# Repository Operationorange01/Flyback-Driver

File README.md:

# Flyback Driver

This is a driver for a High Voltage Flyback Transformer.

We are planning on using it in the next stage in our research on EHD propulsion. You can read our preprint from last year here: https://doi.org/10.31224/6625

## Features:

- Variable duty cycle
- Variable frequency
- Current/Voltage Sensing
- Current/Voltage Regulating 6V to 25V, digitally adjustable via 12-bit DAC about 5mV resolution
- Rotary encoder for control
- OLED Display
- Indicator Lights
- Soft Startup
- Hardware overcurrent protection, independent of firmware
- Latching fault shutdown
- Adjustable trip threshold
- RCD clamp with tunable clamp voltage

## PCB

Made in KiCad. The full schematic is in [assets/schematic.pdf](assets/schematic.pdf).

Main parts:

- **MCU:** STM32F103C8T6
- **Flyback switch:** IRFP460 (500V, 20A) driven by a UCC27511A gate driver
- **Supply regulation:** LM5117 buck controller with two MCP4725 12-bit DACs for digital voltage/current setpoints
- **Sensing:** INA226 current/voltage monitor
- **Protection:** LM393 comparator + 74HC132 latch for hardware overcurrent shutdown
- **Logic rails:** LM2596 and TPS62130 bucks

Custom footprints are in [pcb/libraries](pcb/libraries).

## Firmware

made some basic firmware but is still untested

**disclaimer, most of the firmware was made using the help of ai because I don't know enough c**

## BOM

The full BOM with reference designators, Digi-Key part numbers and datasheets is in [BOM.csv](BOM.csv). Parts on Digi-Key come to about **$94**.

Not on the Digi-Key order yet:

- 1x 0.91" 128x32 I2C OLED (U4)
- 1x 2x4 2.54mm pin header (J1)
- 1x 1x5 2.54mm pin header (J2)
- 16x test points (TP1–TP16)

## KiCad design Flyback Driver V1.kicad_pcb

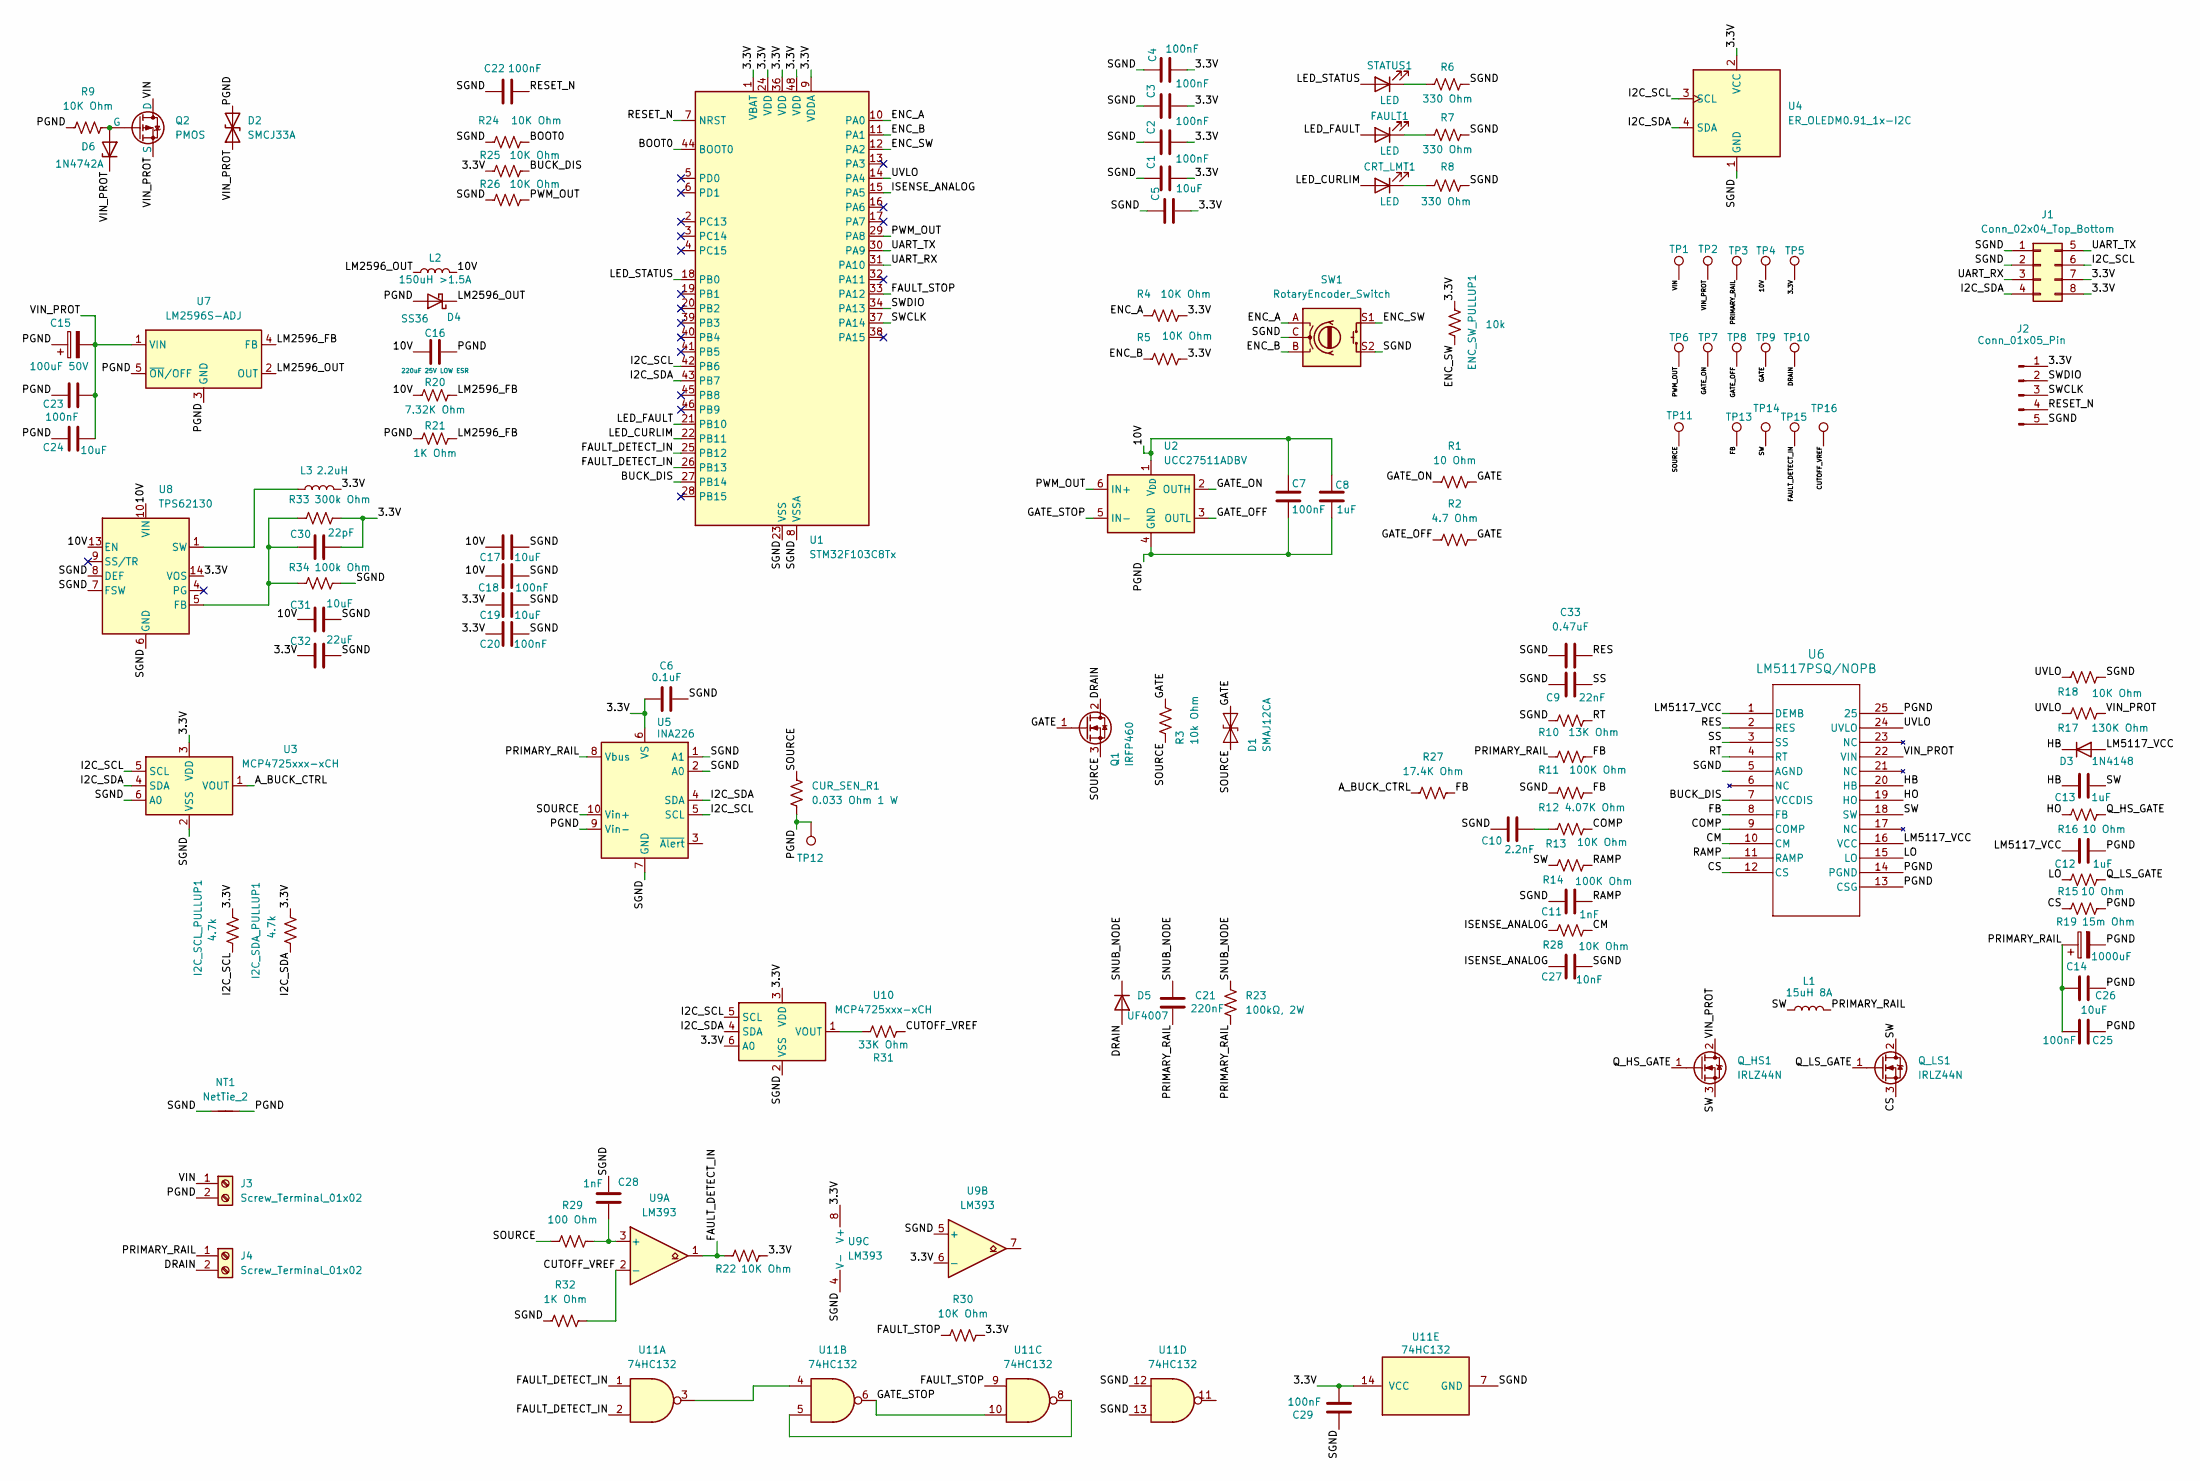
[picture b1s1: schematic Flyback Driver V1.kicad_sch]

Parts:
C1, C2, C3, C4, C7, C18, C20, C22, C23, C25, C29: 100nF; C_0805_2012Metric_Pad1.18x1.45mm_HandSolder
C5, C17, C19, C31: 10uF; C_0805_2012Metric_Pad1.18x1.45mm_HandSolder
C6: 0.1uF; C_0805_2012Metric_Pad1.18x1.45mm_HandSolder
C8, C12, C13: 1uF; C_0805_2012Metric_Pad1.18x1.45mm_HandSolder
C9: 22nF; C_0805_2012Metric_Pad1.18x1.45mm_HandSolder
C10: 2.2nF; C_0805_2012Metric_Pad1.18x1.45mm_HandSolder
C11, C28: 1nF; C_0805_2012Metric_Pad1.18x1.45mm_HandSolder
C14: 1000uF; CP_Radial_D12.5mm_P5.00mm
C15: 100uF 50V; CP_Radial_D8.0mm_P3.50mm
C16: 220uF 25V LOW ESR; CP_Radial_D8.0mm_P3.50mm
C21: 220nF; C_Rect_L18.0mm_W5.0mm_P15.00mm_FKS3_FKP3
C24, C26: 10uF; C_1210_3225Metric_Pad1.33x2.70mm_HandSolder
C27: 10nF; C_0805_2012Metric_Pad1.18x1.45mm_HandSolder
C30: 22pF; C_0805_2012Metric_Pad1.18x1.45mm_HandSolder
C32: 22uF; C_0805_2012Metric_Pad1.18x1.45mm_HandSolder
C33: 0.47uF; C_0805_2012Metric_Pad1.18x1.45mm_HandSolder
CRT_LMT1: LED; LED_0805_2012Metric_Pad1.15x1.40mm_HandSolder
CUR_SEN_R1: 0.033 Ohm 1 W; R_2512_6332Metric_Pad1.40x3.35mm_HandSolder
D1: SMAJ12CA; D_SMA
D2: SMCJ33A; D_SMC
D3: 1N4148; D_DO-35_SOD27_P7.62mm_Horizontal
D4: SS36; D_SMC
D5: UF4007; D_DO-41_SOD81_P10.16mm_Horizontal
D6: 1N4742A; D_DO-41_SOD81_P10.16mm_Horizontal
ENC_SW_PULLUP1: 10k; R_0805_2012Metric_Pad1.20x1.40mm_HandSolder
FAULT1: LED; LED_0805_2012Metric_Pad1.15x1.40mm_HandSolder
I2C_SCL_PULLUP1, I2C_SDA_PULLUP1: 4.7k; R_0805_2012Metric_Pad1.20x1.40mm_HandSolder
J1: Conn_02x04_Top_Bottom; PinHeader_2x04_P2.54mm_Vertical
J2: Conn_01x05_Pin; PinHeader_1x05_P2.54mm_Vertical
J3, J4: Screw_Terminal_01x02; TerminalBlock_Phoenix_MKDS-3-2-5.08_1x02_P5.08mm_Horizontal
L1: 15uH 8A; L_Wurth_WE-XHMA-1090
L2: 150uH >1.5A; INDM125125X800N
L3: 2.2uH; L_Taiyo-Yuden_LCXND4040
NT1: NetTie_2; NetTie-2_SMD_Pad0.5mm
Q1: IRFP460; TO-247-3_Vertical
Q2: PMOS; TO-220-3_Vertical
Q_HS1: IRLZ44N; TO-220-3_Vertical
Q_LS1: IRLZ44N; TO-220-3_Vertical
R1, R15, R16: 10 Ohm; R_0805_2012Metric_Pad1.20x1.40mm_HandSolder
R2: 4.7 Ohm; R_0805_2012Metric_Pad1.20x1.40mm_HandSolder
R3: 10k Ohm; R_0805_2012Metric_Pad1.20x1.40mm_HandSolder
R4, R5, R9, R13, R18, R22, R24, R25, R26, R28, R30: 10K Ohm; R_0805_2012Metric_Pad1.20x1.40mm_HandSolder
R6, R7, R8: 330 Ohm; R_0805_2012Metric_Pad1.20x1.40mm_HandSolder
R10: 13K Ohm; R_0805_2012Metric_Pad1.20x1.40mm_HandSolder
R11, R14: 100K Ohm; R_0805_2012Metric_Pad1.20x1.40mm_HandSolder
R12: 4.07K Ohm; R_0805_2012Metric_Pad1.20x1.40mm_HandSolder
R17: 130K Ohm; R_0805_2012Metric_Pad1.20x1.40mm_HandSolder
R19: 15m Ohm; R_2512_6332Metric_Pad1.40x3.35mm_HandSolder
R20: 7.32K Ohm; R_0805_2012Metric_Pad1.20x1.40mm_HandSolder
R21, R32: 1K Ohm; R_0805_2012Metric_Pad1.20x1.40mm_HandSolder
R23: 100kΩ, 2W; R_Axial_DIN0617_L17.0mm_D6.0mm_P25.40mm_Horizontal
R27: 17.4K Ohm; R_0805_2012Metric_Pad1.20x1.40mm_HandSolder
R29: 100 Ohm; R_0805_2012Metric_Pad1.20x1.40mm_HandSolder
R31: 33K Ohm; R_0805_2012Metric_Pad1.20x1.40mm_HandSolder
R33: 300k Ohm; R_0805_2012Metric_Pad1.20x1.40mm_HandSolder
R34: 100k Ohm; R_0805_2012Metric_Pad1.20x1.40mm_HandSolder
STATUS1: LED; LED_0805_2012Metric_Pad1.15x1.40mm_HandSolder
SW1: RotaryEncoder_Switch; RotaryEncoder_Alps_EC11E-Switch_Vertical_H20mm_MountingHoles
TP1, TP2, TP3, TP4, TP5, TP6, TP7, TP8, TP9, TP10, TP11, TP12, TP13, TP14, TP15, TP16: TestPoint; TestPoint_THTPad_D1.5mm_Drill0.7mm
U1: STM32F103C8Tx; LQFP-48_7x7mm_P0.5mm
U2: UCC27511ADBV; SOT-23-6
U3, U10: MCP4725xxx-xCH; SOT-23-6
U4: ER_OLEDM0.91_1x-I2C
U5: INA226; TSSOP-10_3x3mm_P0.5mm
U6: LM5117PSQ/NOPB; WQFN-24-1EP_4x4mm_P0.5mm_EP2.6x2.6mm_ThermalVias
U7: LM2596S-ADJ; TO-263-5_TabPin3
U8: TPS62130; VQFN-16-1EP_3x3mm_P0.5mm_EP1.68x1.68mm_ThermalVias
U9: LM393; SOIC-8_3.9x4.9mm_P1.27mm
U11: 74HC132; SOIC-14_3.9x8.7mm_P1.27mm

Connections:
/3.3V: C1.2, C2.2, C3.2, C4.2, C5.2, C6.1, C19.1, C20.1, C29.2, C30.2, C32.1, ENC_SW_PULLUP1.1, I2C_SCL_PULLUP1.1, I2C_SDA_PULLUP1.1, J1.7, J1.8, J2.1, L3.2, R4.1, R5.1, R22.2, R25.1, R30.2, R33.2, TP5.1 (1_1), U1.1 (VBAT), U1.9 (VDDA), U1.24 (VDD), U1.36 (VDD), U1.48 (VDD), U3.3 (VDD), U4.2 (VCC), U5.6 (VS), U8.14 (VOS), U9.6 (-), U9.8 (V+), U10.3 (VDD), U10.6 (A0), U11.14 (VCC)
/10V: C7.1, C8.1, C16.1, C17.1, C18.1, C31.1, L2.2, R20.1, TP4.1 (1_1), U2.1 (V_{DD}), U8.10 (VIN), U8.11 (VIN), U8.12 (VIN), U8.13 (EN)
/A_BUCK_CTRL: R27.1, U3.1 (VOUT)
/BOOT0: R24.2, U1.44 (BOOT0)
/BUCK_DIS: R25.2, U1.27 (PB14), U6.7 (VCCDIS)
/CM: R28.2, U6.10 (CM)
/COMP: R13.2, U6.9 (COMP)
/CS: Q_LS1.3 (S), R19.1, U6.12 (CS)
/CUTOFF_VREF: R31.2, R32.2, TP16.1 (1_1), U9.2 (-)
/DRAIN: D5.2 (A), J4.2, Q1.2 (D), TP10.1 (1_1)
/ENC_A: R4.2, SW1.A, U1.10 (PA0)
/ENC_B: R5.2, SW1.B, U1.11 (PA1)
/ENC_SW: ENC_SW_PULLUP1.2, SW1.S1, U1.12 (PA2)
/FAULT_DETECT_IN: R22.1, TP15.1 (1_1), U1.25 (PB12), U1.26 (PB13), U9.1, U11.1, U11.2
/FAULT_STOP: R30.1, U1.33 (PA12), U11.9
/FB: R11.2, R12.2, R27.2, TP13.1 (1_1), U6.8 (FB)
/GATE: D1.2 (A2), Q1.1 (G), R1.2, R2.2, R3.1, TP9.1 (1_1)
/GATE_OFF: R2.1, TP8.1 (1_1), U2.3 (OUTL)
/GATE_ON: R1.1, TP7.1 (1_1), U2.2 (OUTH)
/GATE_STOP: U2.5 (IN-), U11.6, U11.10
/HB: C13.1, D3.1 (K), U6.20 (HB)
/HO: R16.1, U6.19 (HO)
/I2C_SCL: I2C_SCL_PULLUP1.2, J1.6, U1.42 (PB6), U3.5 (SCL), U4.3 (SCL), U5.5 (SCL), U10.5 (SCL)
/I2C_SDA: I2C_SDA_PULLUP1.2, J1.4, U1.43 (PB7), U3.4 (SDA), U4.4 (SDA), U5.4 (SDA), U10.4 (SDA)
/ISENSE_ANALOG: C27.1, R28.1, U1.15 (PA5)
/LED_CURLIM: CRT_LMT1.2 (A), U1.22 (PB11); also elsewhere on the board
/LED_FAULT: FAULT1.2 (A), U1.21 (PB10); also elsewhere on the board
/LED_STATUS: STATUS1.2 (A), U1.18 (PB0); also elsewhere on the board
/LM2596_FB: R20.2, R21.2, U7.4 (FB)
/LM2596_OUT: D4.1 (K), L2.1, U7.2 (OUT)
/LM5117_VCC: C12.1, D3.2 (A), U6.1 (DEMB), U6.16 (VCC)
/LO: R15.1, U6.15 (LO)
/PGND: C7.2, C8.2, C12.2, C14.2, C15.1, C16.2, C23.1, C24.1, C25.1, C26.1, CUR_SEN_R1.2, D2.2 (A2), D4.2 (A), J3.2, NT1.2, R9.1, R19.2, R21.1, TP12.1 (1_1), U2.4 (GND), U5.9 (Vin-), U6.13 (CSG), U6.14 (PGND), U6.25, U7.3 (GND), U7.5 (~ON/OFF)
/PRIMARY_RAIL: C14.1, C21.2, C25.2, C26.2, J4.1, L1.2, R11.1, R23.2, TP3.1 (1_1), U5.8 (Vbus)
/PWM_OUT: R26.2, TP6.1 (1_1), U1.29 (PA8), U2.6 (IN+)
/Q_HS_GATE: Q_HS1.1 (G), R16.2
/Q_LS_GATE: Q_LS1.1 (G), R15.2
/RAMP: C11.2, R14.2, U6.11 (RAMP)
/RES: C33.2, U6.2 (RES)
/RESET_N: C22.2, J2.4, U1.7 (NRST)
/RT: R10.2, U6.4 (RT)
/SGND: C1.1, C2.1, C3.1, C4.1, C5.1, C6.2, C9.1, C10.2, C11.1, C17.2, C18.2, C19.2, C20.2, C22.1, C27.2, C28.1, C29.1, C31.2, C32.2, C33.1, J1.1, J1.2, J2.5, NT1.1, R6.2, R7.2, R8.2, R10.1, R12.1, R18.2, R24.1, R26.1, R32.1, R34.2, SW1.C, SW1.S2, U1.8 (VSSA), U1.23 (VSS), U1.35 (VSS), U1.47 (VSS), U3.2 (VSS), U3.6 (A0), U4.1 (GND), U5.1 (A1), U5.2 (A0), U5.7 (GND), U6.5 (AGND), U8.6 (GND), U8.7 (FSW), U8.8 (DEF), U8.15 (GND), U8.16 (GND), U8.17 (GND), U9.4 (V-), U9.5 (+), U10.2 (VSS), U11.7 (GND), U11.12, U11.13
/SNUB_NODE: C21.1, D5.1 (K), R23.1
/SOURCE: CUR_SEN_R1.1, D1.1 (A1), Q1.3 (S), R3.2, R29.1, TP11.1 (1_1), U5.10 (Vin+)
/SS: C9.2, U6.3 (SS)
/SW: C13.2, L1.1, Q_HS1.3 (S), Q_LS1.2 (D), R14.1, TP14.1 (1_1), U6.18 (SW)
/SWCLK: J2.3, U1.37 (PA14)
/SWDIO: J2.2, U1.34 (PA13)
/UART_RX: J1.3, U1.31 (PA10)
/UART_TX: J1.5, U1.30 (PA9)
/UVLO: R17.1, R18.1, U1.14 (PA4), U6.24 (UVLO)
/VIN: J3.1, Q2.1 (D), TP1.1 (1_1)
/VIN_PROT: C15.2, C23.2, C24.2, D2.1 (A1), D6.1 (K), Q2.3 (S), Q_HS1.2 (D), R17.2, TP2.1 (1_1), U6.22 (VIN), U7.1 (VIN)
unnamed: C10.1, R13.1
unnamed 54: CRT_LMT1.1 (K), R8.1; also elsewhere on the board
unnamed: D6.2 (A), Q2.2 (G), R9.2
unnamed 56: FAULT1.1 (K), R7.1; also elsewhere on the board
unnamed: L3.1, U8.1 (SW), U8.2 (SW), U8.3 (SW)
unnamed 58: R6.1, STATUS1.1 (K); also elsewhere on the board
unnamed: C30.1, R33.1, R34.1, U8.5 (FB)
unnamed: C28.2, R29.2, U9.3 (+)
unnamed: R31.1, U10.1 (VOUT)
unnamed: U11.3, U11.4
unnamed: U11.5, U11.8

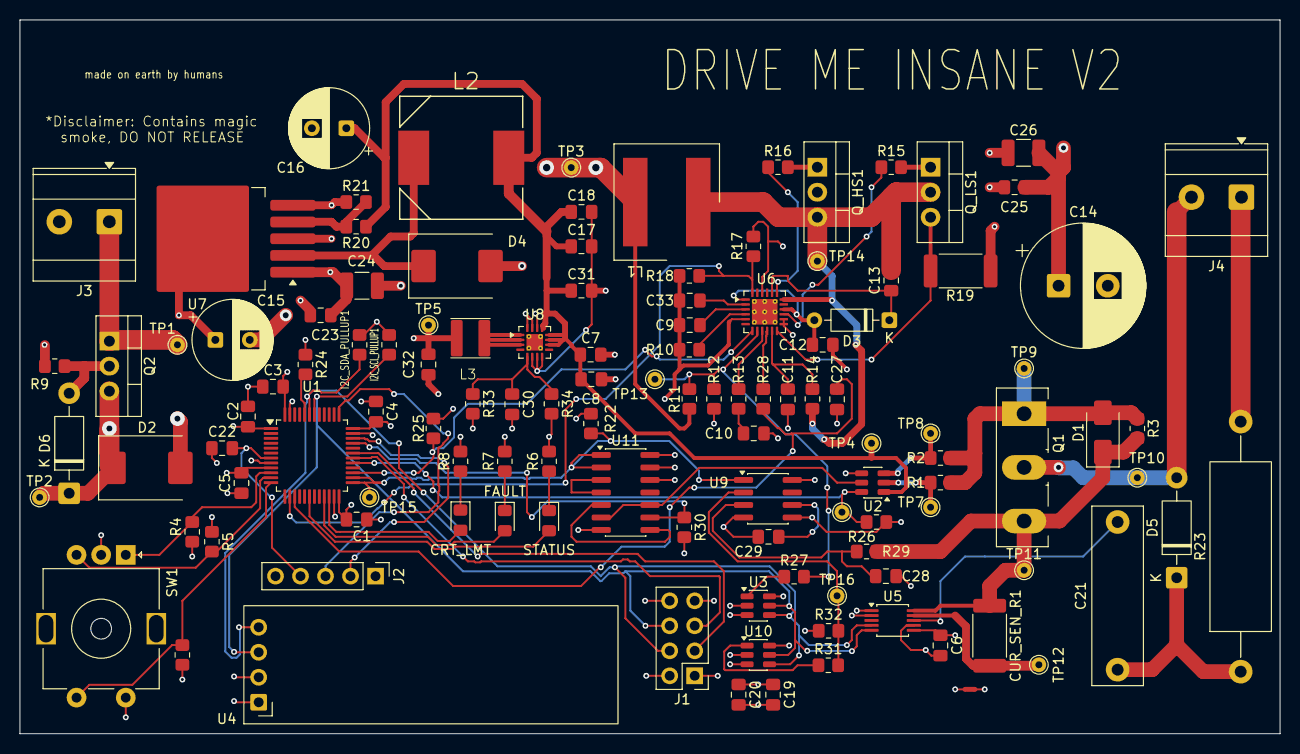
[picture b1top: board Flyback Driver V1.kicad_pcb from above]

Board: 4 copper layers, 128.0 x 72.5 mm, 120 parts (0 on the bottom side), 64 nets.

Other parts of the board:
CRT_LMT: LED; LED_0805_2012Metric_Pad1.15x1.40mm_HandSolder
FAULT: LED; LED_0805_2012Metric_Pad1.15x1.40mm_HandSolder
STATUS: LED; LED_0805_2012Metric_Pad1.15x1.40mm_HandSolder

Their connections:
/LED_CURLIM: CRT_LMT.2 (A); also elsewhere on the board
/LED_FAULT: FAULT.2 (A); also elsewhere on the board
/LED_STATUS: STATUS.2 (A); also elsewhere on the board
unnamed 54: CRT_LMT.1 (K); also elsewhere on the board
unnamed 56: FAULT.1 (K); also elsewhere on the board
unnamed 58: STATUS.1 (K); also elsewhere on the board

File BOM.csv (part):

Reference,Qty Needed,Qty Ordered,Value,Description,Manufacturer,MPN,Digi-Key PN,Unit Price,Datasheet
C1 C2 C3 C4 C7 C18 C20 C22 C23 C25 C29 C6,12,16,100nF,CAP CER 0.1UF 50V X7R 0805,KEMET,C0805C104K5RACTU,399-C0805C104K5RACTUCT-ND,0.09100,https://yageogroup.com/content/datasheet/asset/file/KEM_C100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
C10,1,2,2.2nF,CAP CER 2200PF 50V X7R 0805,KEMET,C0805C222K5RACTU,399-C0805C222K5RACTUCT-ND,0.10000,https://yageogroup.com/content/datasheet/asset/file/KEM_C100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
C11 C28,2,3,1nF,CAP CER 1000PF 50V X7R 0805,Samsung Electro-Mechanics,CL21B102KBANNNC,1276-1020-1-ND,0.10000,https://mm.digikey.com/Volume0/opasdata/d220001/medias/docus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
C14,1,1,1000uF,CAP ALUM 1000UF 20% 50V RADIAL,Nichicon,UVR1H102MHD,493-1111-ND,1.30000,https://www.nichicon.co.jp/english/series_items/catalog_pdf/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
C15,1,1,100uF 50V,CAP ALUM RAD 85C,KEMET,ESK107M063AG3AA,399-ESK107M063AG3AA-ND,0.41000,https://yageogroup.com/content/datasheet/asset/file/KEM_A4004_ESK
C16,1,1,220uF 25V LOW ESR,CAP ALUM 220UF 20% 25V RADIAL TH,Würth Elektronik,860080474010,732-9026-1-ND,0.30000,https://www.we-online.com/components/products/datasheet/8600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
C21,1,1,220nF,CAP FILM 0.22UF 20% 630VDC RAD,TDK,B32922C3224M289,495-B32922C3224M289CT-ND,0.65000,https://product.tdk.com/en/system/files/dam/doc/product/capa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
C24 C26,2,3,10uF,CAP CER 10UF 50V X7R 1210,KEMET,C1210C106K5RACTU,399-C1210C106K5RACTUCT-ND,1.55000,https://yageogroup.com/content/datasheet/asset/file/KEM_C100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
C27,1,2,10nF,CAP CER 10000PF 50V X7R 0805,KEMET,C0805C103K5RACTU,399-C0805C103K5RACTUCT-ND,0.14000,https://yageogroup.com/content/datasheet/asset/file/KEM_C100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
C30,1,2,22pF,CAP CER 22PF 50V C0G/NP0 0805,KEMET,C0805C220J5GACTU,399-C0805C220J5GACTUCT-ND,0.17000,https://yageogroup.com/content/datasheet/asset/file/KEM_C100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
C32,1,2,22uF,CAP CER 22UF 16V X5R 0805,Samsung Electro-Mechanics,CL21A226KOQNNNG,1276-7092-1-ND,0.42000,https://mm.digikey.com/Volume0/opasdata/d220001/medias/docus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
C33,1,2,0.47uF,CAP CER 0.47UF 50V X7R 0805,Samsung Electro-Mechanics,CL21B474KBFNNNG,1276-6482-1-ND,0.10000,http://www.samsungsem.com/kr/support/product-search/mlcc/CL2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
C5 C17 C19 C31,4,6,10uF,CAP CER 10UF 25V X5R 0805,Murata Electronics,GRM21BR61E106MA73L,490-10748-1-ND,0.17000,https://mm.digikey.com/Volume0/opasdata/d220001/medias/docus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
C8 C12 C13,3,5,1uF,CAP CER 1UF 25V X7R 0805,KEMET,C0805C105K3RACTU,399-C0805C105K3RACTUCT-ND,0.16000,https://yageogroup.com/content/datasheet/asset/file/KEM_C100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
C9,1,2,22nF,CAP CER 0.022UF 50V X7R 0805,YAGEO,CC0805KRX7R9BB223,311-1138-1-ND,0.13000,https://yageogroup.com/content/datasheet/asset/file/UPY-GPHC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
CRT_LMT1,1,1,LED,"0805 LED YELLOW 591NM DOMINANT,",QT Brightek (QTB),QBLP631-Y5-2897,1516-QBLP631-Y5-2897CT-ND,0.32000,https://www.qt-brightek.com/datasheet/QBLP631-Y5-2897.pdf
CUR_SEN_R1,1,1,0.033 Ohm 1 W,RES 0.033 OHM 1% 1W 2512,Bourns Inc.,CRF2512-FZ-R033ELF,CRF2512-FZ-R033ELFCT-ND,0.49000,https://www.bourns.com/docs/Product-Datasheets/CRF.pdf
D1,1,1,SMAJ12CA,TVS DIODE 12VWM 19.9VC DO214AC,Littelfuse Inc.,SMAJ12CA,SMAJ12CALFCT-ND,0.48000,https://www.littelfuse.com/assetdocs/tvs-diodes-smaj-datashe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
D2,1,1,SMCJ33A,TVS DIODE 33VWM 53.3VC DO214AB,Littelfuse Inc.,SMCJ33A,SMCJ33ALFCT-ND,0.94000,https://www.littelfuse.com/assetdocs/littelfuse_tvs_diode_sm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
D3,1,1,1N4148,DIODE STANDARD 100V 200MA DO35,onsemi,1N4148,1N4148FS-ND,0.10000,https://www.onsemi.com/pub/Collateral/1N914-D.PDF
D4,1,1,SS36,DIODE SCHOTTKY 60V 3A DO214AB,Taiwan Semiconductor Corporation,SS36,1801-SS36CT-ND,0.79000,https://services.taiwansemi.com/storage/resources/datasheet/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
D5,1,1,UF4007,DIODE STANDARD 1000V 1A DO204AL,Taiwan Semiconductor Corporation,UF4007,1801-UF4007CT-ND,0.42000,https://services.taiwansemi.com/storage/resources/datasheet/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
D6,1,1,1N4742A,DIODE ZENER 12V 1W DO41,onsemi,1N4742A,1N4742AFS-ND,0.28000,https://www.onsemi.com/pdf/datasheet/1n4736at-d.pdf
ENC_SW_PULLUP1 R3 R4 R5 R9 R13 R18 R22 R24 R25 R26 R28 R30,13,15,10k,RES 10K OHM 1% 1/4W 0805,"KOA Speer Electronics, Inc.",RK73H2ATTD1002F,2019-RK73H2ATTD1002FCT-ND,0.03400,https://www.koaspeer.com/pdfs/RK73H.pdf
FAULT1,1,1,LED,"0805 LED RED 625NM DOMINANT, 631",QT Brightek (QTB),QBLP631-R5-2897,1516-QBLP631-R5-2897CT-ND,0.23000,https://www.qt-brightek.com/datasheet/QBLP631-R5-2897.pdf
I2C_SCL_PULLUP1 I2C_SDA_PULLUP1,2,3,4.7k,RES 4.7K OHM 1% 1/4W 0805,"KOA Speer Electronics, Inc.",RK73H2ATTDD4701F,2019-RK73H2ATTDD4701FCT-ND,0.10000,https://www.koaspeer.com/pdfs/RK73H.pdf
J1,1,,Conn_02x04_Top_Bottom,NOT SOURCED,,,,,
J2,1,,Conn_01x05_Pin,NOT SOURCED,,,,,
J3 J4,2,2,Screw_Terminal_01x02,TERM BLK 2P SIDE ENT 5.08MM PCB,Phoenix Contact,1711725,277-1027-ND,1.81000,https://www.phoenixcontact.com/us/products/1711725/pdf
L1,1,1,15uH 8A,FIXED IND 15UH 8.3A 14.8 MOHM,Würth Elektronik,78439369150,732-78439369150CT-ND,5.27000,https://www.we-online.com/components/products/datasheet/7843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
L2,1,1,150uH >1.5A,FIXED IND 150UH 1.59A 247 MOHM,Eaton - Electronics Division,DR127-151-R,283-DR127-151-RCT-ND,0.88000,https://www.eaton.com/content/dam/eaton/products/electronic-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
L3,1,1,2.2uH,FIXED IND 2.2UH 2.2A 42 MOHM SMD,Taiyo Yuden,LCXND4040TKL2R2MDG,587-LCXND4040TKL2R2MDGCT-ND,0.30000,https://mm.digikey.com/Volume0/opasdata/d220001/medias/docus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
Q1,1,2,IRFP460,MOSFET N-CH 500V 20A TO247-3,Vishay Siliconix,IRFP460PBF,IRFP460PBF-ND,9.39000,https://www.vishay.com/docs/91237/91237.pdf
Q2,1,1,PMOS,MOSFET P-CH 55V 74A TO220AB,Infineon Technologies,IRF4905PBF,IRF4905PBF-ND,3.26000,https://www.infineon.com/dgdl/irf4905pbf.pdf?fileId=5546d462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
Q_HS1 Q_LS1,2,2,IRLZ44N,MOSFET N-CH 55V 47A TO220AB,Infineon Technologies,IRLZ44NPBF,IRLZ44NPBF-ND,1.80000,https://www.infineon.com/dgdl/irlz44npbf.pdf?fileId=5546d462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
R1 R15 R16,3,5,10 Ohm,RES 10 OHM 1% 1/4W 0805,"KOA Speer Electronics, Inc.",RK73H2ATTD10R0F,2019-RK73H2ATTD10R0FCT-ND,0.10000,https://www.koaspeer.com/pdfs/RK73H.pdf
R10,1,2,13K Ohm,RES SMD 13K OHM 1% 1/8W 0805,TE Connectivity Passive Product,CRG0805F13K,A126339CT-ND,0.10000,https://www.te.com/commerce/DocumentDelivery/DDEController?A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
R11 R14 R34,3,5,100K Ohm,RES 100K OHM 1% 1/4W 0805,"KOA Speer Electronics, Inc.",RK73H2ATTD1003F,2019-RK73H2ATTD1003FCT-ND,0.10000,https://www.koaspeer.com/pdfs/RK73H.pdf
R12,1,2,4.07K Ohm,RES SMD 4.12K OHM 1% 1/8W 0805,Vishay Dale,CRCW08054K12FKEA,541-4.12KCCT-ND,0.10000,https://www.vishay.com/docs/20035/dcrcwe3.pdf
R17,1,2,130K Ohm,RES 130K OHM 1% 1/8W 0805,YAGEO,RC0805FR-07130KL,311-130KCRCT-ND,0.10000,https://yageogroup.com/content/datasheet/asset/file/PYU-RC_G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
R19,1,1,15m Ohm,RES 0.015 OHM 1% 1W 2512,Vishay Dale,WSL2512R0150FEA,WSLG-.015CT-ND,1.34000,https://www.vishay.com/docs/30100/wsl.pdf
R2,1,2,4.7 Ohm,RES 4.7 OHM 1% 1/4W 0805,"KOA Speer Electronics, Inc.",RK73H2ATTD4R70F,2019-RK73H2ATTD4R70FCT-ND,0.10000,https://www.koaspeer.com/pdfs/RK73H.pdf
R20,1,2,7.32K Ohm,RES 7.32K OHM 1% 1/8W 0805,YAGEO,RC0805FR-077K32L,311-7.32KCRCT-ND,0.10000,https://yageogroup.com/content/datasheet/asset/file/PYU-RC_G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
R21 R32,2,3,1K Ohm,RES 1K OHM 1% 1/4W 0805,"KOA Speer Electronics, Inc.",RK73H2ATTD1001F,2019-RK73H2ATTD1001FCT-ND,0.10000,https://www.koaspeer.com/pdfs/RK73H.pdf
R23,1,1,"100kΩ, 2W",RES 100K OHM 5% 2W AXIAL,Stackpole Electronics Inc,RSMF2JT100K,RSMF2JT100KCT-ND,0.19000,https://www.seielect.com/catalog/SEI-RSF_RSMF.pdf
R27,1,2,17.4K Ohm,RES 17.4K OHM 1% 1/8W 0805,Stackpole Electronics Inc,RMCF0805FT17K4,RMCF0805FT17K4CT-ND,0.11000,https://www.seielect.com/catalog/SEI-RMCF_RMCP.pdf
R29,1,4,100 Ohm,RES 100 OHM 1% 1/8W 0805,YAGEO,RC0805FR-07100RL,311-100CRCT-ND,0.10000,https://yageogroup.com/content/datasheet/asset/file/PYU-RC_G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
R31,1,2,33K Ohm,RES 33K OHM 1% 1/8W 0805,Stackpole Electronics Inc,RMCF0805FT33K0,RMCF0805FT33K0CT-ND,0.10000,https://www.seielect.com/catalog/SEI-RMCF_RMCP.pdf
R33,1,2,300k Ohm,RES 300K OHM 1% 1/4W 0805,"KOA Speer Electronics, Inc.",RK73H2ATTD3003F,2019-RK73H2ATTD3003FCT-ND,0.10000,https://www.koaspeer.com/pdfs/RK73H.pdf
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
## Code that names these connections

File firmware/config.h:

/*
 * config.h - every tunable and every hardware constant in one place.
 *
 * Hardware values come from "Flyback driver netlist v2" (KiCad 10) and BOM.csv.
 * If you change a resistor on the board, change it here too.
 */
#ifndef CONFIG_H
#define CONFIG_H

#define FW_VERSION          "1.0.0"

/* ------------------------------------------------------------------ */
/* Clock: there is no crystal on the board (PD0/PD1 unconnected), so   */
/* the MCU runs from HSI/2 x 16 = 64 MHz (the HSI maximum on F103).    */
/* ------------------------------------------------------------------ */
#define SYSCLK_HZ           64000000UL

/* ------------------------------------------------------------------ */
/* Supply rail                                                         */
/* "3.3V" net is made by TPS62130 with R33 = 300k / R34 = 100k and     */
/* Vfb = 0.8 V  ->  0.8 * (1 + 300/100) = 3.20 V.  Both MCP4725 DACs   */
/* use VDD as their reference, so DAC math uses this value.            */
/* ------------------------------------------------------------------ */
#define VDD_NOMINAL_MV      3200
#define USE_VREFINT_FOR_VDD 0       /* 1 = use measured VDD (internal ref, +-3 %) */

/* ------------------------------------------------------------------ */
/* LM5117 primary-rail setpoint network                                */
/*   PRIMARY_RAIL --R11-- FB --R12-- SGND,   DAC U3 --R27-- FB          */
/*   Vout = 0.8 + R11 * (0.8/R12 + (0.8 - Vdac)/R27)                   */
/* Higher DAC code = LOWER output voltage.                             */
/* ------------------------------------------------------------------ */
#define FB_VREF_V           0.8f
#define R11_OHM             100000.0f
#define R12_OHM             4120.0f   /* BOM part CRCW08054K12 (schematic says 4.07k) */
#define R27_OHM             17400.0f

/* ------------------------------------------------------------------ */
/* Hardware over-current trip (LM393 U9A + 74HC latch U11)             */
/*   CUTOFF_VREF = Vdac(U10) * R32 / (R31 + R32)                       */
/*   trips when I_switch * RSENSE > CUTOFF_VREF                        */
/* ------------------------------------------------------------------ */
#define R31_OHM             33000.0f
#define R32_OHM             1000.0f
#define RSENSE_OHM          0.033f    /* CUR_SEN_R1, also the INA226 shunt */

/* ------------------------------------------------------------------ */
/* VIN sense on PA4 (shared with LM5117 UVLO pin)                      */
/*   VIN_PROT --R17-- UVLO/PA4 --R18-- SGND                            */
/* LM5117 sources 20 uA into this node once UVLO > 1.25 V.             */
/* ------------------------------------------------------------------ */
#define R17_OHM             130000.0f
#define R18_OHM             10000.0f
#define UVLO_HYST_A         20e-6f
#define UVLO_THRESH_V       1.25f
#define VIN_UVLO_MV         17500     /* 1.25 V * (1 + R17/R18): buck will not start below this */

/* LM5117 current monitor: CM -> R28/C27 -> PA5.  Vcm ~= Iout*RS*AS.    */
/* Only valid in continuous conduction; used for telemetry only.       */
#define LM5117_RS_OHM       0.015f    /* R19 */
#define LM5117_AS           10.0f

/* ------------------------------------------------------------------ */
/* I2C bus (PB6 = SCL, PB7 = SDA, bit-banged, 4.7k pull-ups)           */
/* ------------------------------------------------------------------ */
#define I2C_ADDR_DAC_VSET   0x60      /* U3  MCP4725A0, A0 = SGND -> sets PRIMARY_RAIL */
#define I2C_ADDR_DAC_TRIP   0x61      /* U10 MCP4725A0, A0 = 3V3  -> sets OCP threshold */
#define I2C_ADDR_INA226     0x40      /* U5, A0 = A1 = SGND */
#define I2C_ADDR_OLED       0x3C      /* U4 SSD1306 128x32 */
#define I2C_SPEED_HZ        200000UL

/* INA226: AVG = 16, VBUSCT = VSHCT = 1.1 ms, continuous shunt+bus.    */
/* One result every ~35 ms.  The switch current is pulsed, the INA226  */
/* integrates it, so the reading is the average primary current.      */
#define INA226_CONFIG       0x4527

/* ------------------------------------------------------------------ */
/* Operating limits (user settings are clamped to these)               */
/* ------------------------------------------------------------------ */
#define VSET_MIN_MV         6500      /* hardware floor is ~6.4 V at VDD = 3.2 V */
#define VSET_MAX_MV         24500     /* hardware ceiling is ~24.8 V */
#define VOUT_ABS_MAX_MV     27000     /* OVP: immediate fault above this */
#define OVP_MARGIN_MV       3000      /* OVP: fault if rail stays this far above command */
#define OVP_SAMPLES         10        /* ... for this many INA226 samples (~350 ms) */

#define FREQ_MIN_HZ         500
#define FREQ_MAX_HZ         150000
#define DUTY_MAX_X10        500       /* 50.0 % hard ceiling on on-time (core reset) */

#define ILIM_MIN_MA         50
#define ILIM_MAX_MA         2400      /* INA226 full scale is 81.92 mV / 0.033 = 2.48 A */
#define TRIP_MIN_MA         100
#define TRIP_MAX_MA         2800      /* DAC full scale gives ~2.85 A */
#define SS_MAX_MS           10000

/* Factory defaults */
#define DEF_FREQ_HZ         20000
#define DEF_DUTY_X10        100       /* 10.0 % */
#define DEF_VSET_MV         12000
#define DEF_ILIM_MA         1000
#define DEF_TRIP_MA         2000
#define DEF_SS_MS           1000

/* ------------------------------------------------------------------ */
/* Control loop                                                        */
/* ------------------------------------------------------------------ */
#define CTRL_PERIOD_MS      5
#define CC_GAIN_MV_PER_MA   5         /* rail drop per mA over the limit, per sample */
#define CC_MAX_STEP_MV      2000
#define CC_RECOVER_MV       100       /* rail recovery per sample when under limit */
#define CC_FAIL_SAMPLES     15        /* at min voltage and still >110% limit -> fault */
#define VTRIM_ENABLE        1         /* trim DAC so the INA226-measured rail matches Vset */
#define VTRIM_MAX_MV        1000      /* covers ~4 % gain error at 24 V */
#define VTRIM_WINDOW_MV     1000
#define VSLEW_MV_PER_TICK   100       /* 20 V/s max rail slew */
#define DUTY_SLEW_PER_TICK  5         /* 0.5 % per 5 ms = 100 %/s */
#define SENSOR_TIMEOUT_MS   300
#define TRIP_DISABLES_BUCK  1         /* a hardware OCP trip also shuts the LM5117 off */

/* ------------------------------------------------------------------ */
/* User interface                                                      */
/* ------------------------------------------------------------------ */
#define ENC_COUNTS_PER_DETENT 2       /* EC11E15244B2: 15 pulses / 30 detents. Use 4 if one click = two steps */
#define ENC_REVERSE         0         /* 1 if clockwise turns values down */
#define ENC_FAST_MS         40        /* detents closer than this count x10 */
#define BTN_DEBOUNCE_MS     20
#define BTN_LONG_MS         800
#define UI_FRAME_MS         100
#define UI_EDIT_TIMEOUT_MS  10000

#define UART_BAUD           115200

#endif
